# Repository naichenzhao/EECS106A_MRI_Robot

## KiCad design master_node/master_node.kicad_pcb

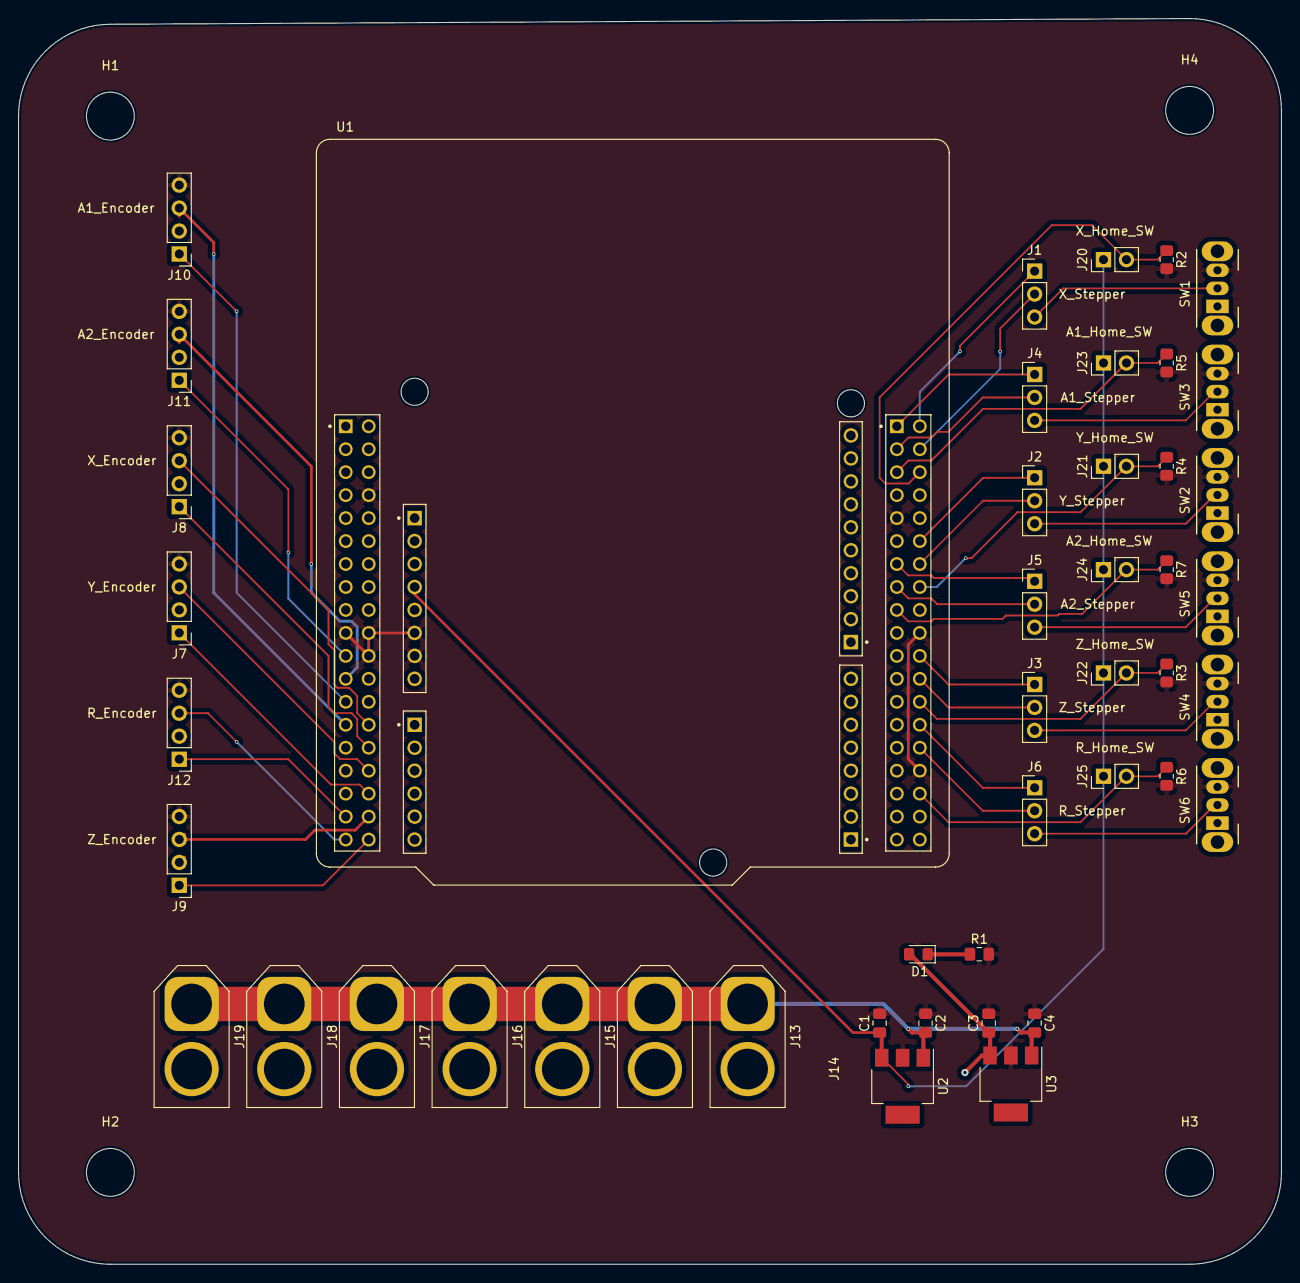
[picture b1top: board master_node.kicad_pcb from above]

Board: 2 copper layers, 139.7 x 137.8 mm, 50 parts (0 on the bottom side), 41 nets.

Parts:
C1, C3: .1 uF; C_0805_2012Metric_Pad1.18x1.45mm_HandSolder
C2, C4: .33 uF; C_0805_2012Metric_Pad1.18x1.45mm_HandSolder
D1: LED; LED_0805_2012Metric_Pad1.15x1.40mm_HandSolder
H1, H2, H3, H4: MountingHole; MountingHole_5.3mm_M5_DIN965
J1: X_Stepper; PinHeader_1x03_P2.54mm_Vertical
J2: Y_Stepper; PinHeader_1x03_P2.54mm_Vertical
J3: Z_Stepper; PinHeader_1x03_P2.54mm_Vertical
J4: A1_Stepper; PinHeader_1x03_P2.54mm_Vertical
J5: A2_Stepper; PinHeader_1x03_P2.54mm_Vertical
J6: R_Stepper; PinHeader_1x03_P2.54mm_Vertical
J7: Y_Encoder; PinHeader_1x04_P2.54mm_Vertical
J8: X_Encoder; PinHeader_1x04_P2.54mm_Vertical
J9: Z_Encoder; PinHeader_1x04_P2.54mm_Vertical
J10: A1_Encoder; PinHeader_1x04_P2.54mm_Vertical
J11: A2_Encoder; PinHeader_1x04_P2.54mm_Vertical
J12: R_Encoder; PinHeader_1x04_P2.54mm_Vertical
J13: XT60-in; AMASS_XT60-F_1x02_P7.20mm_Vertical
J14: X_Power; AMASS_XT60-F_1x02_P7.20mm_Vertical
J15: Y _Power; AMASS_XT60-F_1x02_P7.20mm_Vertical
J16: Z_Power; AMASS_XT60-F_1x02_P7.20mm_Vertical
J17: A1_Power; AMASS_XT60-F_1x02_P7.20mm_Vertical
J18: A2_Power; AMASS_XT60-F_1x02_P7.20mm_Vertical
J19: R_Power; AMASS_XT60-F_1x02_P7.20mm_Vertical
J20: X_Home_SW; PinHeader_1x02_P2.54mm_Vertical
J21: Y_Home_SW; PinHeader_1x02_P2.54mm_Vertical
J22: Z_Home_SW; PinHeader_1x02_P2.54mm_Vertical
J23: A1_Home_SW; PinHeader_1x02_P2.54mm_Vertical
J24: A2_Home_SW; PinHeader_1x02_P2.54mm_Vertical
J25: R_Home_SW; PinHeader_1x02_P2.54mm_Vertical
R1: 290; C_0805_2012Metric_Pad1.18x1.45mm_HandSolder
R2, R3, R4, R5, R6, R7: 10k; R_0805_2012Metric_Pad1.20x1.40mm_HandSolder
SW1: X_Enable; SW_CuK_OS102011MA1QN1_SPDT_Angled
SW2: Y_Enable; SW_CuK_OS102011MA1QN1_SPDT_Angled
SW3: A1_Enable; SW_CuK_OS102011MA1QN1_SPDT_Angled
SW4: Z_Enable; SW_CuK_OS102011MA1QN1_SPDT_Angled
SW5: A2_Enable; SW_CuK_OS102011MA1QN1_SPDT_Angled
SW6: R_Enable; SW_CuK_OS102011MA1QN1_SPDT_Angled
U1: NUCLEO-F446RE; MODULE_NUCLEO-F446RE
U2: UA78M33CDCYR; SOT-223
U3: UA78M05IDCYR; SOT-223

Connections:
+3.3V: C1.1, J20.1, J21.1, J22.1, J23.1, J24.1, J25.1, U1.CN6_4 (CN6_+3V3), U2.3 (OUT)
+5V: C3.1, D1.2 (A), J7.2, J8.2, J9.2, J10.2, J11.2, J12.2, SW1.1 (A), SW2.1 (A), SW3.1 (A), SW4.1 (A), SW5.1 (A), SW6.1 (A), U3.3 (OUT)
+24V: C2.2, C4.2, J13.1, J14.1, J15.1, J16.1, J17.1, J18.1, J19.1, U2.1 (IN), U3.1 (IN)
/A1_A: J10.3, U1.CN7_27 (PC15)
/A1_B: J10.1, U1.CN7_25 (PC14)
/A1_Dir: J4.2, U1.CN10_3 (PB8)
/A1_Home: J23.2, R5.1, U1.CN10_5 (PB9)
/A1_Pulse: J4.1, U1.CN10_1 (PC9)
/A2_A: J11.3, U1.CN7_23 (PC13)
/A2_B: J11.1, U1.CN7_21 (PB7)
/A2_Dir: J5.2, U1.CN10_15 (PA7)
/A2_Home: J24.2, R7.1, U1.CN10_17 (PB6)
/A2_Pulse: J5.1, U1.CN10_13 (PA6)
/R_A: J12.3, U1.CN7_37 (PC3)
/R_B: J12.1, U1.CN7_35 (PC2)
/R_Dir: J6.2, U1.CN10_30 (PB13)
/R_Home: J25.2, R6.1, U1.CN10_34 (PC4)
/R_Pulse: J6.1, U1.CN10_28 (PB14)
/X_A: J8.3, U1.CN7_28 (PA0)
/X_B: J8.1, U1.CN7_30 (PA1)
/X_Dir: J1.2, U1.CN10_4 (PC6)
/X_Home: J20.2, R2.1, U1.CN10_6 (PC5)
/X_Pulse: J1.1, U1.CN10_2 (PC8)
/Y_A: J7.3, U1.CN7_32 (PA4)
/Y_B: J7.1, U1.CN7_34 (PB0)
/Y_Dir: J2.2, U1.CN10_14 (PA11)
/Y_Home: J21.2, R4.1, U1.CN10_16 (PB12)
/Y_Pulse: J2.1, U1.CN10_12 (PA12)
/Z_A: J9.3, U1.CN7_36 (PC1/PB9)
/Z_B: J9.1, U1.CN7_38 (PC0/PB8)
/Z_Dir: J3.2, U1.CN10_24 (PB1)
/Z_Home: J22.2, R3.1, U1.CN10_26 (PB15)
/Z_Pulse: J3.1, U1.CN10_22 (PB2)
GND: C1.2, C2.1, C3.2, C4.1, J7.4, J8.4, J9.4, J10.4, J11.4, J12.4, J13.2, J14.2, J15.2, J16.2, J17.2, J18.2, J19.2, R1.2, R2.2, R3.2, R4.2, R5.2, R6.2, R7.2, SW1.3 (C), SW2.3 (C), SW3.3 (C), SW4.3 (C), SW5.3 (C), SW6.3 (C), U1.CN6_6 (CN6_GND), U1.CN6_7 (CN6_GND), U1.CN7_8 (CN7_GND), U1.CN7_19 (CN7_GND), U1.CN7_20 (CN7_GND), U1.CN7_22 (CN7_GND), U1.CN10_9 (CN10_GND), U1.CN10_20 (CN10_GND), U1.CN10_32 (AGND), U2.2 (GND), U3.2 (GND)
unnamed: D1.1 (K), R1.1
unnamed: J1.3, SW1.2 (B)
unnamed: J2.3, SW2.2 (B)
unnamed: J3.3, SW4.2 (B)
unnamed: J4.3, SW3.2 (B)
unnamed: J5.3, SW5.2 (B)
unnamed: J6.3, SW6.2 (B)

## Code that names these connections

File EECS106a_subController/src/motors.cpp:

// motor.cpp
#include <Arduino.h>
#include <AccelStepper.h>

#include "motors.h"



//  + -- -- -- -- -- -- -- -- -- -- -- -- -- -- -- -- -- -- -- - +
//  | Define ports for stepper motors and homing flags
//  + -- -- -- -- -- -- -- -- -- -- -- -- -- -- -- -- -- -- -- - +
#define motorInterfaceType 1

#define X_PULSE PC8
#define X_DIR PC6
#define X_HOME PC5

#define Y_PULSE PA12
#define Y_DIR PA11
#define Y_HOME PB12

#define Z_PULSE PB2
#define Z_DIR PB1
#define Z_HOME PB15

#define R_PULSE PB14
#define R_DIR PB13
#define R_HOME PC4

#define A1_PULSE PC9
#define A1_DIR PB8
#define A1_HOME PB9

#define A2_PULSE PA6
#define A2_DIR PA7
#define A2_HOME PB6

const int MAX_SPEED = 10000;
const int MAX_ACCELERATION = 1000;

const int homing_step = 100;
const int homing_backoff_step = 1;

//  + -- -- -- -- -- -- -- -- -- -- -- -- -- -- -- -- -- -- -- - +
//  | Setup Steppers
//  + -- -- -- -- -- -- -- -- -- -- -- -- -- -- -- -- -- -- -- - +

// Steppers for the gantry
AccelStepper x_stepper = AccelStepper(motorInterfaceType, X_PULSE, X_DIR);
AccelStepper y_stepper = AccelStepper(motorInterfaceType, Y_PULSE, Y_DIR);
AccelStepper z_stepper = AccelStepper(motorInterfaceType, Z_PULSE, Z_DIR);

// Rotary stepper
AccelStepper r_stepper = AccelStepper(motorInterfaceType, R_PULSE, R_DIR);

// Steppers for the arm
AccelStepper a1_stepper = AccelStepper(motorInterfaceType, A1_PULSE, A1_DIR);
AccelStepper a2_stepper = AccelStepper(motorInterfaceType, A2_PULSE, A2_DIR);



//  + -- -- -- -- -- -- -- -- -- -- -- -- -- -- -- -- -- -- -- - +
//  | Stepper Motor
//  + -- -- -- -- -- -- -- -- -- -- -- -- -- -- -- -- -- -- -- - +

void setupMotors()
{
    // setup constant values for steppers
    x_stepper.setMaxSpeed(MAX_SPEED);
    x_stepper.setAcceleration(MAX_ACCELERATION);

    y_stepper.setMaxSpeed(MAX_SPEED);
    y_stepper.setAcceleration(MAX_ACCELERATION);

    z_stepper.setMaxSpeed(MAX_SPEED);
    z_stepper.setAcceleration(MAX_ACCELERATION);

    r_stepper.setMaxSpeed(MAX_SPEED);
    r_stepper.setAcceleration(MAX_ACCELERATION);

    a1_stepper.setMaxSpeed(MAX_SPEED);
    a1_stepper.setAcceleration(MAX_ACCELERATION);

    a2_stepper.setMaxSpeed(MAX_SPEED);
    a2_stepper.setAcceleration(MAX_ACCELERATION);

    // set input for all homing pins
    pinMode(X_HOME, INPUT);
    pinMode(Y_HOME, INPUT);
    pinMode(Z_HOME, INPUT);
    pinMode(R_HOME, INPUT);
    pinMode(A1_HOME, INPUT);
    pinMode(A2_HOME, INPUT);

}

void homeMotors() {
    homeSingleStepper(&x_stepper, X_HOME);
    homeSingleStepper(&y_stepper, Y_HOME);
    homeSingleStepper(&z_stepper, Z_HOME);
    homeSingleStepper(&r_stepper, R_HOME);
    homeSingleStepper(&a1_stepper, A1_HOME);
    homeSingleStepper(&a2_stepper, A2_HOME);
}

void set_motors(int positions[]) {
    // Takes in array of length 6, each it the position of a stepper motor
    moveSingleStepper(&x_stepper, positions[0]);
    moveSingleStepper(&y_stepper, positions[1]);
    moveSingleStepper(&z_stepper, positions[2]);
    moveSingleStepper(&r_stepper, positions[3]);
    moveSingleStepper(&a1_stepper, positions[4]);
    moveSingleStepper(&a2_stepper, positions[5]);
}

void set_x_motor(int pos) {
    moveSingleStepper(&x_stepper, pos);
}
void set_y_motor(int pos) {
    moveSingleStepper(&y_stepper, pos);
}
void set_z_motor(int pos) {
    moveSingleStepper(&z_stepper, pos);
}
void set_r_motor(int pos) {
    moveSingleStepper(&r_stepper, pos);
}
void set_a1_motor(int pos) {
    moveSingleStepper(&a1_stepper, pos);
}
void set_a2_motor(int pos) {
    moveSingleStepper(&a2_stepper, pos);
}




//  + -- -- -- -- -- -- -- -- -- -- -- -- -- -- -- -- -- -- -- - +
//  | Helper Functions
//  + -- -- -- -- -- -- -- -- -- -- -- -- -- -- -- -- -- -- -- - +

void moveSingleStepper(AccelStepper* stepper, int pos){
    stepper->moveTo(pos);
    stepper->run();
}

void homeSingleStepper(AccelStepper* stepper, int switch_port){
    // home x_stepper
    while (!digitalRead(switch_port))
    {
        stepper->moveTo(stepper->currentPosition() - homing_step);
        stepper->run();
        delay(5);
    }
    stepper->stop();
    while (digitalRead(switch_port))
    {
        stepper->moveTo(stepper->currentPosition() + homing_backoff_step);
        stepper->run();
        delay(1);
    }
    stepper->stop();
    stepper->setCurrentPosition(0);
}

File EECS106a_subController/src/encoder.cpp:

// encoder.cpp
#include "encoder.h"

//  + -- -- -- -- -- -- -- -- -- -- -- -- -- -- -- -- -- -- -- - +
//  | Define ports for encoders
//  + -- -- -- -- -- -- -- -- -- -- -- -- -- -- -- -- -- -- -- - +

#define X_A PA0
#define X_B PA1

#define Y_A PA4
#define Y_B PB0

#define Z_A PC1
#define Z_B PC0

#define R_A PC3
#define R_B PC2

#define A1_A PC15
#define A1_B PC14

#define A2_A PC13
#define A2_B PC7

volatile long X_COUNTER = 0;
volatile long Y_COUNTER = 0;
volatile long Z_COUNTER = 0;
volatile long R_COUNTER = 0;
volatile long A1_COUNTER = 0;
volatile long A2_COUNTER = 0;



//  + -- -- -- -- -- -- -- -- -- -- -- -- -- -- -- -- -- -- -- - +
//  | Encoder Functions
//  + -- -- -- -- -- -- -- -- -- -- -- -- -- -- -- -- -- -- -- - +

void setupEncoders() {
    // Set all A ports to internal pullup
    pinMode(X_A, INPUT_PULLUP);
    pinMode(Y_A, INPUT_PULLUP);
    pinMode(Z_A, INPUT_PULLUP);
    pinMode(R_A, INPUT_PULLUP);
    pinMode(A1_A, INPUT_PULLUP);
    pinMode(A2_A, INPUT_PULLUP);

    // Attach respective interrupts to each encoder
    attachInterrupt(digitalPinToInterrupt(X_A), pulseX, RISING);
    attachInterrupt(digitalPinToInterrupt(Y_A), pulseY, RISING);
    attachInterrupt(digitalPinToInterrupt(Z_A), pulseZ, RISING);
    attachInterrupt(digitalPinToInterrupt(R_A), pulseR, RISING);
    attachInterrupt(digitalPinToInterrupt(A1_A), pulseA1, RISING);
    attachInterrupt(digitalPinToInterrupt(A2_A), pulseA2, RISING);
}

// Overall reset function
void resetEncoders() {
    X_COUNTER = 0;
    Y_COUNTER = 0;
    Z_COUNTER = 0;
    R_COUNTER = 0;
    A1_COUNTER = 0;
    A2_COUNTER = 0;
}

// Reset function for each encoder
void reset_x() {
    X_COUNTER = 0;
}
void reset_y() {
    Y_COUNTER = 0;
}
void reset_z() {
    Z_COUNTER = 0;
}
void reset_r() {
    R_COUNTER = 0;
}
void reset_a1() {
    A1_COUNTER = 0;
}
void reset_a2() {
    A2_COUNTER = 0;
}

// getters for each encoder
long get_x() {
    return X_COUNTER;
}
long get_y() {
    return Y_COUNTER;
}
long get_z() {
    return Z_COUNTER;
}
long get_r() {
    return R_COUNTER;
}
long get_a1() {
    return A1_COUNTER;
}
long get_a2() {
    return A2_COUNTER;
}



//  + -- -- -- -- -- -- -- -- -- -- -- -- -- -- -- -- -- -- -- - +
//  | Encoder Interrupt Functions
//  + -- -- -- -- -- -- -- -- -- -- -- -- -- -- -- -- -- -- -- - +

void pulseX() {
    X_COUNTER += digitalRead(X_B) ? 1 : -1;
}
void pulseY() {
    Y_COUNTER += digitalRead(Y_B) ? 1 : -1;
}
void pulseZ() {
    Z_COUNTER += digitalRead(Z_B) ? 1 : -1;
}
void pulseR() {
    R_COUNTER += digitalRead(R_B) ? 1 : -1;
}
void pulseA1() {
    A1_COUNTER += digitalRead(A1_B) ? 1 : -1;
}
void pulseA2() {
    A2_COUNTER += digitalRead(A2_B) ? 1 : -1;
}

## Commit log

2023-10-21 low level firmware done
2023-10-21 updated names
2023-10-22 got rid of extra files
2023-10-29 initial ros workspace
2023-10-30 pcb work, some
2023-11-01 did communication between ros and arduino
2023-11-02 schematic done and footprints assigned
2023-11-03 finished layout with clearance violations
2023-11-04 too late, I am done
2023-11-04 ron fearing added
2023-11-05 stuff
2023-11-05 PCB updates
2023-11-08 imporoved low level control for multi stepper
2023-11-22 updated pub
2023-11-23 first draft for encoder homing and PID control
2023-11-25 tested PID controllers for steppers
2023-11-27 test urdf export
2023-11-27 updated urdf export
2023-11-27 put urdf into ros project
2023-11-27 Robot is now in MoveIt
2023-11-27 current test for basic server for interface with moveit
2023-11-29 I want to kill myself
2023-11-29 IK with moveit works
2023-12-01 new URDF
2023-12-01 updated URDF file
2023-12-01 another commit
2023-12-01 we can feed encoder data into rviz now
2023-12-02 created new package
2023-12-02 added gui point selector
2023-12-02 i hate quaternions
2023-12-02 slight modification to ik code
2023-12-03 planner draft and robot working with all joints
2023-12-05 basic planner works, committing before refactor
2023-12-05 commit before more changes
2023-12-05 we have basic full path planning integration built in
2023-12-06 head_pub draft
2023-12-06 head works!
2023-12-06 now in terms of world frame
2023-12-06 slicing half of the face
2023-12-06 kill myself
2023-12-06 pviz
2023-12-06 point cloud workinggit add *
2023-12-06 another update
2023-12-06 Add .gitignore for ROS build and devel directories
2023-12-06 Remove existing build and devel directories
2023-12-06 Consolidate tams_wireless_ft and transform_ft into wireless_ft
2023-12-06 integration with head gui
2023-12-06 close to done
2023-12-10 Create basic website
2023-12-13 Update website
2023-12-13 More website updates/adding cycloidal drive CAD
2023-12-13 Further website updates
2023-12-14 Remove vrpn_client_ros for submodule issue
2023-12-14 Readd vrpn_client_ros
2023-12-14 Restructure website data
2023-12-16 Update website slightly
